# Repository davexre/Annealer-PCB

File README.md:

# Annealer PCB
 An Arduino shield for induction cartridge case annealers based on the GinaErick design. 

## Pictures!

- [Front of board design](images/AnnealerPCBv3-front.png)
- [Back of board design](images/AnnealerPCBv3-back.png)

Final boards will actually print with an inductor symbol on the front and back, too - OSH Park's rendering doesn't 
show it correctly. Pictures of the actual boards will replace the images here when they arrive.

## Origins
 This design began from a simple DIY induction based cartridge case annealer created by a couple people on the
 [accurateshooter.com forum](http://forum.accurateshooter.com/threads/induction-brass-annealer-redux.3908353/). 
 Get ready for some reading - as of this writing, that thread is over 103 pages long!
 
 After creating a working, basic, analog annealer, I decided it was time to convert the thing to digital 
 control, and started implementing Arduino based controls. That naturally led to implementing the Arduino
 shield here to make it easier and cleaner to hook up the Arduino to all of the necessary hardware.
 
 ## Features
 - Arduino Uno R3 format shield
 - Support for boards with 5v, 3.3v, and 2v ADCs
 - Sensors
   - Two thermistors
   - Voltage
   - Current
   - Two [break beam sensors](https://www.adafruit.com/product/2167)
 - Two buttons (typically, Start and Stop) via a 4-pin header
 - Two relays (typically, for Induction board and solenoid control)
 - Two auxiliary headers (signal pin and ground, could be used for a variety of control purposes)
 - Multipurpose header (3 signals and ground, can hook up an encoder with button, or any other use)
 - Two LEDs for troubleshooting and confirmation of code
 - I2C connector to add an LCD or other I2C based device
 - Power On LED connector for front panel
 - Reset button
 
 You can find a [Bill of Materials](BOM.md) in this repository, too.
 
 ## IMPORTANT NOTE
 
 If you use the I2C connector, be aware that you cannot use Proximity sensor 2 or Thermistor 2 on some boards (like
 the Arduino Uno). Any board that ties SDA and SCL pins to A4/A5 will encounter this issue. I recommend that you pick the
 functions you wish to use, and only install connectors or headers for those functions (ie, only install the I2C connector
 **or** the Proximity 2 and Thermistor 2 connectors!

 ## Example Implementation
 My code for implementation is here: https://github.com/davexre/Annealer-Control - note that I don't make use of 
 all of the features on this board at this time! 
 
 ## Configuration
 The board was originally designed with [SparkFun's](https://www.sparkfun.com/) [RedBoard Artemis](https://www.sparkfun.com/products/15444)
 in mind. The Artemis processor has ADCs that use 2v as their reference. They can safely handle 
 3.3v, but saturate at 2v. So, the board incorporates several voltage dividers to keep things within
 the scale that the ADCs can successfully read. The documentation here covers ways to configure the
 board for other reference voltages. There are four solderable open/closed jumper pads that you can
 use to alter several circuit paths appropriately. SparkFun has a [tutorial on using jumper pads](https://learn.sparkfun.com/tutorials/how-to-work-with-jumper-pads-and-pcb-traces) on their site.
 
 ### Pin Map
 ```
#ifdef _V4_BOARD
  #define  VOLTAGE_PIN     A0
  #define  CURRENT_PIN     A1
  #define  THERM1_PIN      A2
  #define  OPTO1_PIN       A3
  #define  THERM2_PIN      A4
  #define  OPTO2_PIN       A5
  #define  START_PIN       2   
  #define  STOP_PIN        3
  #define  INDUCTOR_PIN    4
  #define  SOLENOID_PIN    5
  #define  AUX1_PIN        6
  #define  AUX2_PIN        7   
  #define  INDUCTOR_LED    8
  #define  SOLENOID_LED    9
  #define  ENCODER_A_PIN   10
  #define  ENCODER_B_PIN   11
  #define  ENCODER_BUTTON  12
#endif
```

 ### Voltage
 Input to pin A0.
 
 The voltage sensor circuit expects to be fed by a voltage divider - I'm using an Octopus Voltage Divider Brick,
 which is a 16:1 voltage divider (see below). For a 48v power supply on the annealer, that means a maximum input voltage of 4v
 coming in to J1 on the board. The design then incoporates a second voltage divider using a 10k resistor and a 20k
 trimpot, so you can adjust the input voltage precisely to match the ADC (so, exactly 50% for the Artemis). 
 
 However, if you board supports 3.3v, you can set the trimpot to cut 4v down to 3.3v. For a 5v board, you can bypass the 
 on-board voltage divider completely by cutting the VOL-BYPASS jumper, and soldering the other side closed. This will
 pass the input on J1 directly to A0. Be careful! 
 
 It may also be possible to use the onboard voltage divider to cut the voltage back to anything reasonable. The design
 uses a [Bourns 3296W](https://www.bourns.com/pdfs/3296.pdf) trimpot, which is available in resistances up to 2Mohm.
 A 200kOhm trimpot could be used (instead of the spec'ed 20kOhm trimpot) in conjunction with the specified 10kOhm resistor
 to bring 48v in line with the ADC. But... I prefer to keep higher voltage off the shield, thus the voltage brick. 
 
 To tune the voltage divider after assembly, attach 5v to pin 1 at connector J1. Measure the voltage between A0 and GND.
 Tune trimpot VR1 until you measure 2.5v, indicating that the voltage divider network is dividing voltage by 2 exactly. 
 
 *Note:* it seems like the Octopus Voltage Divider Brick is no longer made by ElecFreaks. So, 
 I [ginned up another PCB design](https://github.com/davexre/Voltage-Divider-Brick) that implements something very
 similar to the Octopus brick. You can substitute whatever resistors you need to get the output voltage within the scale
 that your board can support. You could potentially just use the voltage divider already on the Annealer board to replace
 it, but personally, I prefer to keep potentially damaging voltages (pun intended) away from my main board. The brick 
 adds a small layer of protection, in this case.
 
 ### Current
 Input to pin A1.
 
 The current sensor circuit expects to receive the output from something like a Hall effect sensor, such as the [Gravity
 20A Current Sensor](https://www.dfrobot.com/product-1570.html) made by DF Robot. The pinout on J2 expects to power a 
 device, so pin 1 is 5V supply. Pin 2 is ground. Pin 3 is the return from the [ACS712 Hall effect sensor IC](http://www.allegromicro.com/~/media/Files/Datasheets/ACS712-Datasheet.ashx?la=en). The sensor returns 
 1/2 of the supply voltage at 0A (and can signal +/- 20A). At +20A, it returns 4.5v. 
 
 If you have a 5v board, you can safely bypass the voltage divider network by cutting the CUR-BYPASS jumper and soldering
 the other side closed. 
 
 For other boards, the voltage divider can be tuned to pull the max input value down to match the ADC reference voltage.
 Divide your reference voltage by 4.5 to get the scale factor, and then multiply by 5 to get a target voltage. For instance, 
 for the Artemis, 2/4.5 = .444. Multiply by 5v to get a target of 2.222 volts. For 3.3V reference, your target is 3.667.
 Attach 5v to pin 3 on J2, and then measure voltage between A1 and GND. Tune trimpot VR2 until you reach the target voltage. 
 
 For using sensors other than the Gravity sensor block lined above, you can use this circuit as needed. Changing the jumper
 setting links pin 3 on J2 to A1 directly, or you can simply use the voltage divider network to configure the correct input
 voltage for your sensor. 
 
 ### REF-VOLT jumper
 
 The REF-VOLT jumper feeds the thermistor and proximity sensors an appropriate logic level voltage for the board
 in use. To get accurate readings, and avoid damage to your board, you need to supply these devices with your reference
 voltage. 
 
 The default setting is 3.3v - you can easily cut the jumper and solder to the 5.5v side, as well.
 
 To configure for 5v, cut both the REF_VOLT jumper and resolder the opposite side. This connects the 5v
 supply to the thermistor voltage divider.

 ### Thermistors
 Input to pins A2 and A4, respectively. _**SEE NOTE ABOVE ABOUT I2C**_
 
 These are basic 10K nominal thermistors. They're generally used by wiring them in a voltage divider configuration with a
 10k resistor, and determining the resistance of the thermistor at the current temperature, and then cross referencing that
 to a table, or using a Steinhart style equation to arrive at the actual temperature. One example of [this kind of thermistor](https://www.adafruit.com/product/372_)
 is sold by Adafruit. 
 
 There's also a voltage divider feeding the thermistors to ensure they get the correct logic level voltage. That's easy if
 you have a 3.3v or 5v board. If you have an Artemis based board, though, you need to supply a  2v reference for accurate
 readings. So, we do that with a voltage divider on the board. By default, the board divides 3.3v (from the REF-VOLT jumper)
 down to 2v for the source voltage.
 
 To set this up, feed 3.3v into the 3.3v pin on the shield. Then probe the middle pad of the THERM_DIV jumper and GND.
 Adjust VR3 until you reach 2v.
 
 See "REF-VOLT jumper" above to determine how to send the correct source voltage to the thermistors. If you need to bypass 
 the voltage divider (to send 3.3v or 5v directly to the thermistors), cut the THERM-DIV jumper and solder to the other
 side. 

 ### Proximity Sensors
 Input to pins A3 and A5, respectively. _**SEE NOTE ABOVE ABOUT I2C**_
 
 J3 and J10 are both 5 pin jumpers that are intended to drive the [Adafruit IR Break Beam sensors](https://www.adafruit.com/product/2167). 
 
 Pin 1 connects to a digital pin, so you'll need to use A3 and A5 with digitalRead. You need to set INPUT_PULLUP on 
 those pins, as well. Pin 2 should be your reference voltage (3.3v or 5v) and is set by the REF-VOLT jumper (see above). 
 Pin 4 is 5v for the IR transmitter. Pins 3 and 5 are ground.

 ### Start/Stop buttons, relays, AUX, and Encoder connectors
 
 Each of these connectors provides direct access to one or more digital pins. You can use these for input or output as
 required. The example implementation uses the start/stop buttons, and the relays, currently. 
 
 J8 is a 4 pin connector with pins 2 & 4 connected to GND. Pin 1 connects to D6, and Pin 3 connects to D7. The intention
 here is to connect each pair to a basic momentary switch/button and use them for control over the anneal cycle. You likely
 want to use the INPUT_PULLUP option on the pin configuration, or implement your own pullup or pulldown resistor for each
 pin. 
 
 J6, J7, J9, and J11 are all two pin connectors. Pin 2 on each connects to GND. Pin 1 connects as follows: J6 - D4, J7 - D5,
 J9 - D2, J11 - D3. The example uses J6 and J7 to operate the inductor board SSR, and the trapdoor solenoid SSR, 
 respectively.
 
 The Encoder connector provides access to 3 additional digital pins (D10 on pin 1, D11 on pin 2, D12 on pin3), with
 the fourth pin connecting to GND. This could be used for any purpose required, but one common purpose might be to interface
 with an encoder knob and click switch. 

 ### I2C
 
 _**SEE NOTE ABOVE ABOUT PIN CONFLICTS WITH I2C AND OTHER DEVICES**_
 
 The I2C connector breaks out GND on pin 1, VCC (selectable 3.3V or 5V) on pin 2, SDA on pin 3, and SCL on pin 4, similar
 to the pin order found on common I2C LCDs. This gives you a way to connect any I2C device to your board. Between this and
 the Multipurpose connector, you can easily implement an LCD and clickable encoder for input and display. 
 
 There's a solderable jumper for voltage selection. It defaults to 3.3v, with 5V selectable on the other side of the jumper.
 Obviously, use the correct voltage for your device(s)!

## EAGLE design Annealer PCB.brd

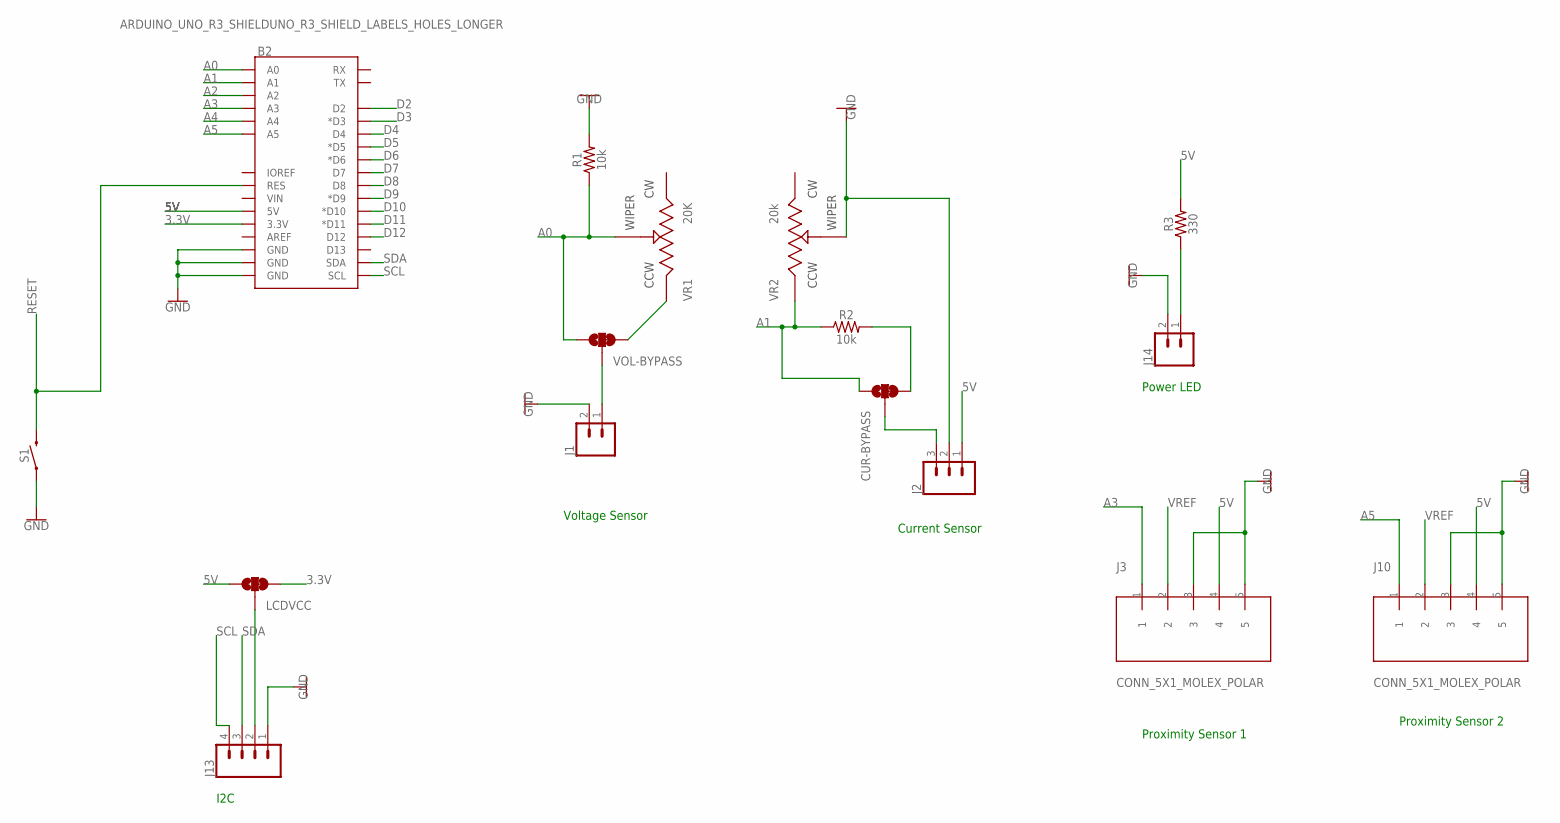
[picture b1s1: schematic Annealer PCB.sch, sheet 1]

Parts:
B2: ARDUINO_UNO_R3_SHIELDUNO_R3_SHIELD_LABELS_HOLES_L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; UNO_R3_SHIELD_HOLES_LONGER
CUR-BYPASS: JUMPER-SMT_3_1-NC_TRACE_SILK; SMT-JUMPER_3_1-NC_TRACE_SILK
J1, J14: CONN_02POLAR; MOLEX-1X2
J2: CONN_03POLAR; MOLEX-1X3
J3, J10: CONN_5X1_MOLEX_POLAR; MOLEX-5
J13: CONN_04POLAR; MOLEX-1X4
LCDVCC: JUMPER-SMT_3_1-NC_TRACE_SILK; SMT-JUMPER_3_1-NC_TRACE_SILK
R1, R2: 10k; AXIAL-0.3
R3: 330; AXIAL-0.3
S1: MOMENTARY-SWITCH-SPST-PTH-6.0MM; TACTILE_SWITCH_PTH_6.0MM
VOL-BYPASS: JUMPER-SMT_3_1-NC_TRACE_SILK; SMT-JUMPER_3_1-NC_TRACE_SILK
VR1: 20K; W
VR2: 20k; W

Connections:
3.3V: B2.3.3V, LCDVCC.3; also elsewhere on the board
5V: B2.5V, J2.1, J3.4, J10.4, LCDVCC.1, R3.P$2 (2); also elsewhere on the board
A0: B2.A0, R1.P$1 (1), VOL-BYPASS.1, VR1.2
A1: B2.A1, CUR-BYPASS.1, R2.P$1 (1), VR2.1
A2: B2.A2; also elsewhere on the board
A3: B2.A3, J3.1
A4: B2.A4; also elsewhere on the board
A5: B2.A5, J10.1
D2: B2.D2; also elsewhere on the board
D3: B2.D3 (*D3); also elsewhere on the board
D4: B2.D4; also elsewhere on the board
D5: B2.D5 (*D5); also elsewhere on the board
D6: B2.D6 (*D6); also elsewhere on the board
D7: B2.D7; also elsewhere on the board
D8: B2.D8; also elsewhere on the board
D9: B2.D9 (*D9); also elsewhere on the board
D10: B2.D10 (*D10); also elsewhere on the board
D11: B2.D11 (*D11); also elsewhere on the board
D12: B2.D12; also elsewhere on the board
GND: B2.GND@0 (GND), B2.GND@1 (GND), B2.GND@2 (GND), J1.2, J2.2, J3.3, J3.5, J10.3, J10.5, J13.1, J14.2, R1.P$2 (2), S1.1, VR2.2; also elsewhere on the board
unnamed: J14.1, R3.P$1 (1)
unnamed: CUR-BYPASS.2, J2.3
unnamed: CUR-BYPASS.3, R2.P$2 (2)
unnamed: VOL-BYPASS.3, VR1.1
unnamed: J1.1, VOL-BYPASS.2
unnamed: J13.2, LCDVCC.2
RESET: B2.RES, S1.3 (2)
SCL: B2.SCL, J13.4
SDA: B2.SDA, J13.3
VREF: J3.2, J10.2; also elsewhere on the board

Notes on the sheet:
Current Sensor
Voltage Sensor
Proximity Sensor 1
Proximity Sensor 2
I2C
Power LED

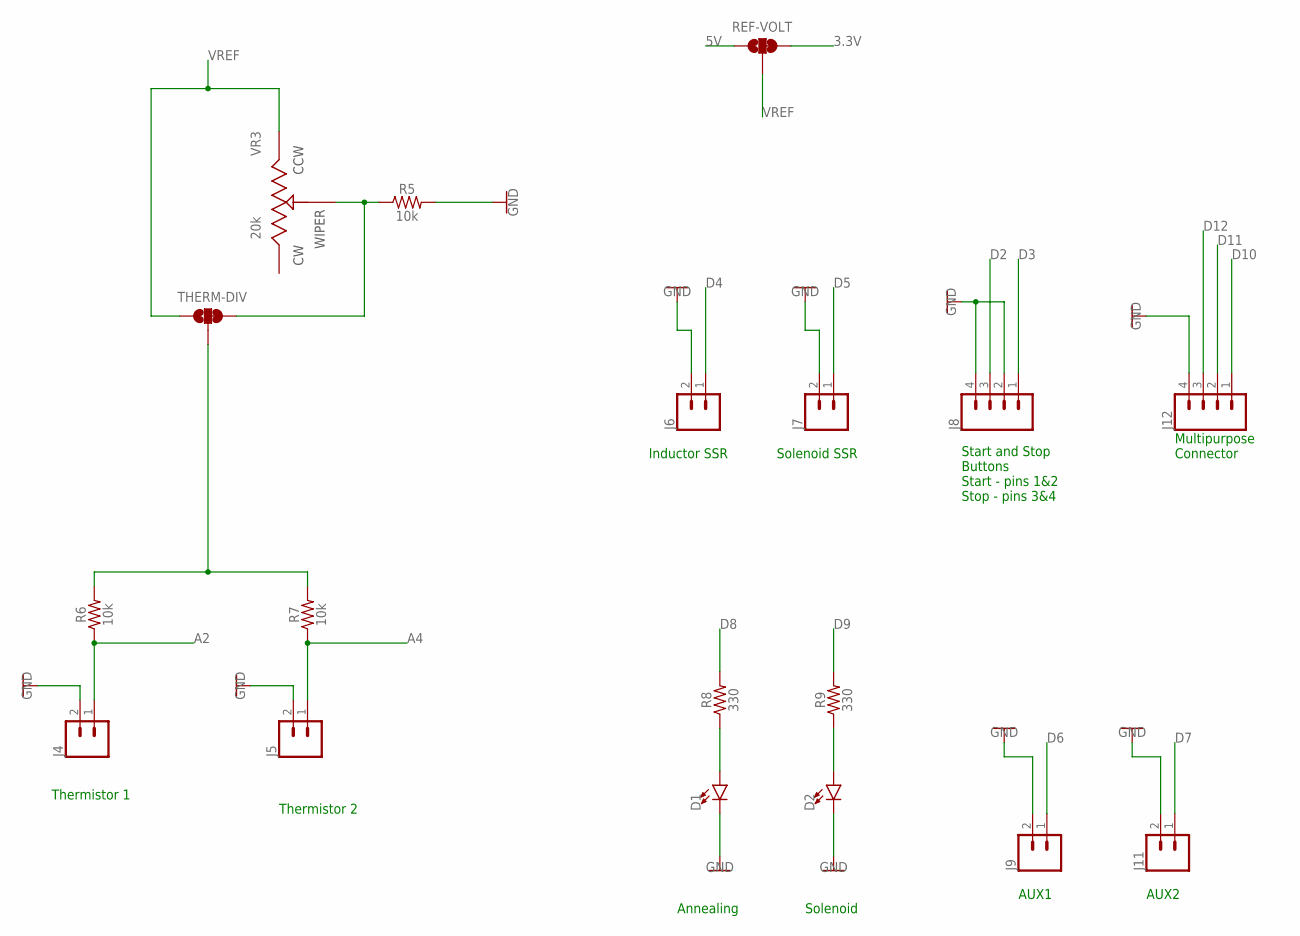
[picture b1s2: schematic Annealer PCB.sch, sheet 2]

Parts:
D1, D2: LED5MM; LED_5MM
J4, J5, J6, J7, J9, J11: CONN_02POLAR; MOLEX-1X2
J8, J12: CONN_04POLAR; MOLEX-1X4
R5, R6, R7: 10k; AXIAL-0.3
R8, R9: 330; AXIAL-0.3
REF-VOLT: JUMPER-SMT_3_1-NC_TRACE_SILK; SMT-JUMPER_3_1-NC_TRACE_SILK
THERM-DIV: JUMPER-SMT_3_1-NC_TRACE_SILK; SMT-JUMPER_3_1-NC_TRACE_SILK
VR3: 20k; W

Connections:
3.3V: REF-VOLT.3; also elsewhere on the board
5V: REF-VOLT.1; also elsewhere on the board
A2: J4.1, R6.P$1 (1); also elsewhere on the board
A4: J5.1, R7.P$1 (1); also elsewhere on the board
D2: J8.3; also elsewhere on the board
D3: J8.1; also elsewhere on the board
D4: J6.1; also elsewhere on the board
D5: J7.1; also elsewhere on the board
D6: J9.1; also elsewhere on the board
D7: J11.1; also elsewhere on the board
D8: R8.P$2 (2); also elsewhere on the board
D9: R9.P$2 (2); also elsewhere on the board
D10: J12.1; also elsewhere on the board
D11: J12.2; also elsewhere on the board
D12: J12.3; also elsewhere on the board
GND: D1.K (C), D2.K (C), J4.2, J5.2, J6.2, J7.2, J8.2, J8.4, J9.2, J11.2, J12.4, R5.P$2 (2); also elsewhere on the board
unnamed: D1.A, R8.P$1 (1)
unnamed: D2.A, R9.P$1 (1)
unnamed: R5.P$1 (1), THERM-DIV.3, VR3.2
SRC: R6.P$2 (2), R7.P$2 (2), THERM-DIV.2
VREF: REF-VOLT.2, THERM-DIV.1, VR3.1; also elsewhere on the board

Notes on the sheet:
Thermistor 1
Thermistor 2
Inductor SSR
Solenoid SSR
Annealing
Solenoid
Start and Stop Buttons Start - pins 1&2 Stop - pins 3&4
AUX1
AUX2
Multipurpose Connector

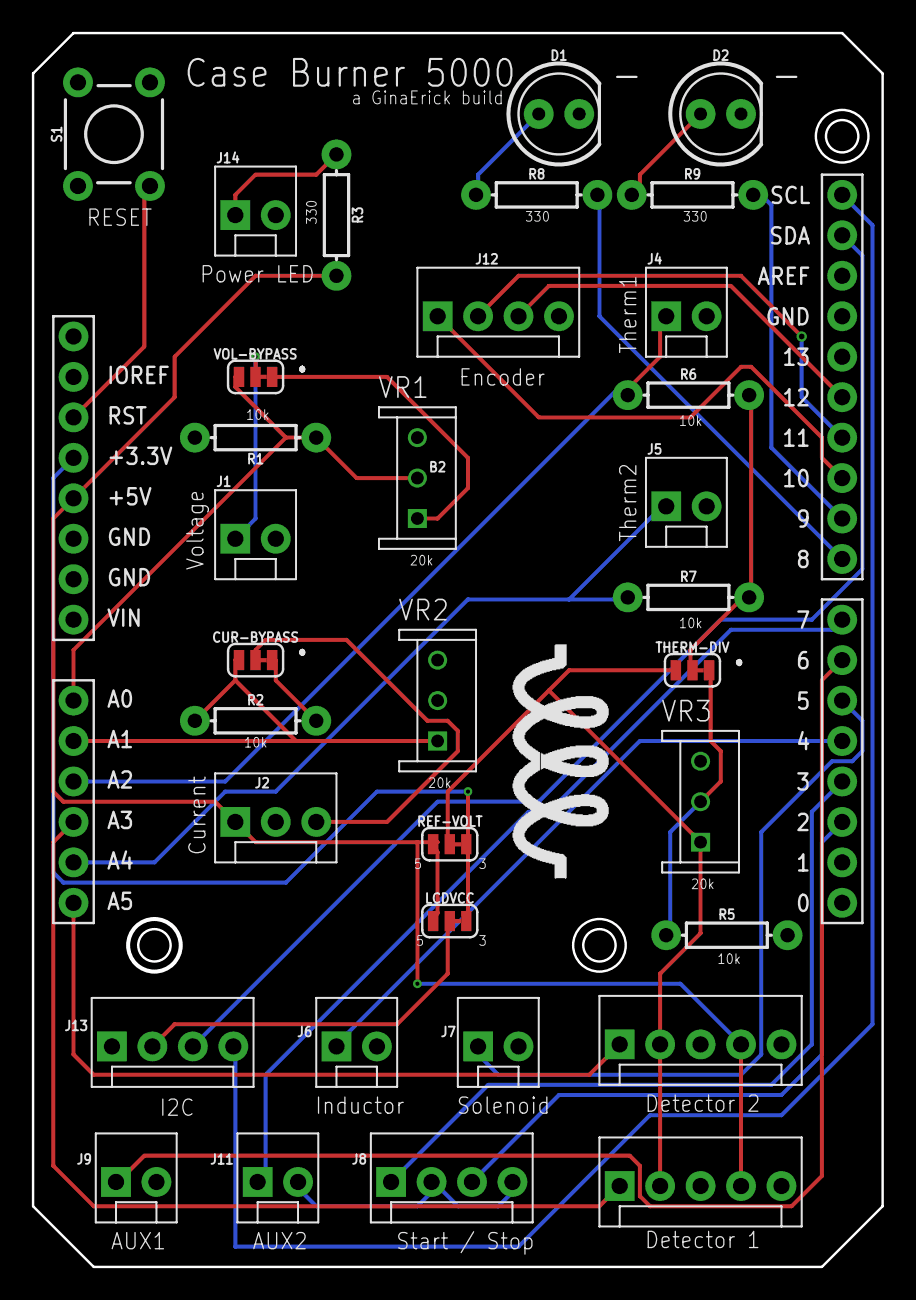
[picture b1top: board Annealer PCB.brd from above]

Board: 2 copper layers, 53.2 x 77.4 mm, 34 parts (0 on the bottom side), 34 nets.

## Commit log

2020-05-15 Initial upload
    v3 of PCB design. Initial final.
2020-05-16 Added I2C for an LCD or similar
2020-05-16 Swap pins on thermistor2 and prox2
2020-05-17 Inlcuding BOM CSV
2020-05-17 Added additional silkscreen
    Added additional documentation on bottom silkscreen layer.
2020-05-17 Added headers
2020-05-18 Change to correct license text for GPL
2020-05-18 Update on resistors vs. trimpot
2020-05-18 Add board images
2020-05-18 Added render pictures
2020-05-18 Add voltage divider brick design
2020-05-26 Project description
2020-05-26 v3.1 - source voltage for phototransistors
    Source voltage was only 5v on v3.0. Changed design so that source voltage for thermistors AND phototransistors on the proximity sensors is fed by an appropriate reference voltage.
2020-05-29 v3.2 - source voltage for proximity detectors
    Changed voltage handling for proximity sensors to avoid disrupting thermistor measurements when a phototransistor detects light inbound. Each phototransistor should have it's own input source and vol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
2020-05-30 v3.2 - minor trace movement
2020-05-31 Fixed hole sizes and moved things accordingly
2020-06-03 Added pin map
2020-06-03 bad markdown
2020-06-04 Not a Stevie Ray Vaughn voltage divider
2020-06-08 Added PDF print of schematic
2020-06-12 Update for v4 board
2020-06-12 Update to v4
2020-06-12 v4 board update
2020-06-14 4.1 - add power-on LED
2020-06-14 Add connector for power-on LED
2020-06-14 Add feature for Power On LED
2020-06-14 Label for Power ON LED

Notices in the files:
parts and their libraries:
SparkFun-Connectors: Licensing: Creative Commons ShareAlike 4.0 International - https://creativecommons.org/licenses/by-sa/4.0
Volks73-Bourns: Creative Commons Attribution-ShareAlike 3.0 Unported (CC BY-SA 3.0), http://creativecommons.org/licenses/by-sa/3.0/.
